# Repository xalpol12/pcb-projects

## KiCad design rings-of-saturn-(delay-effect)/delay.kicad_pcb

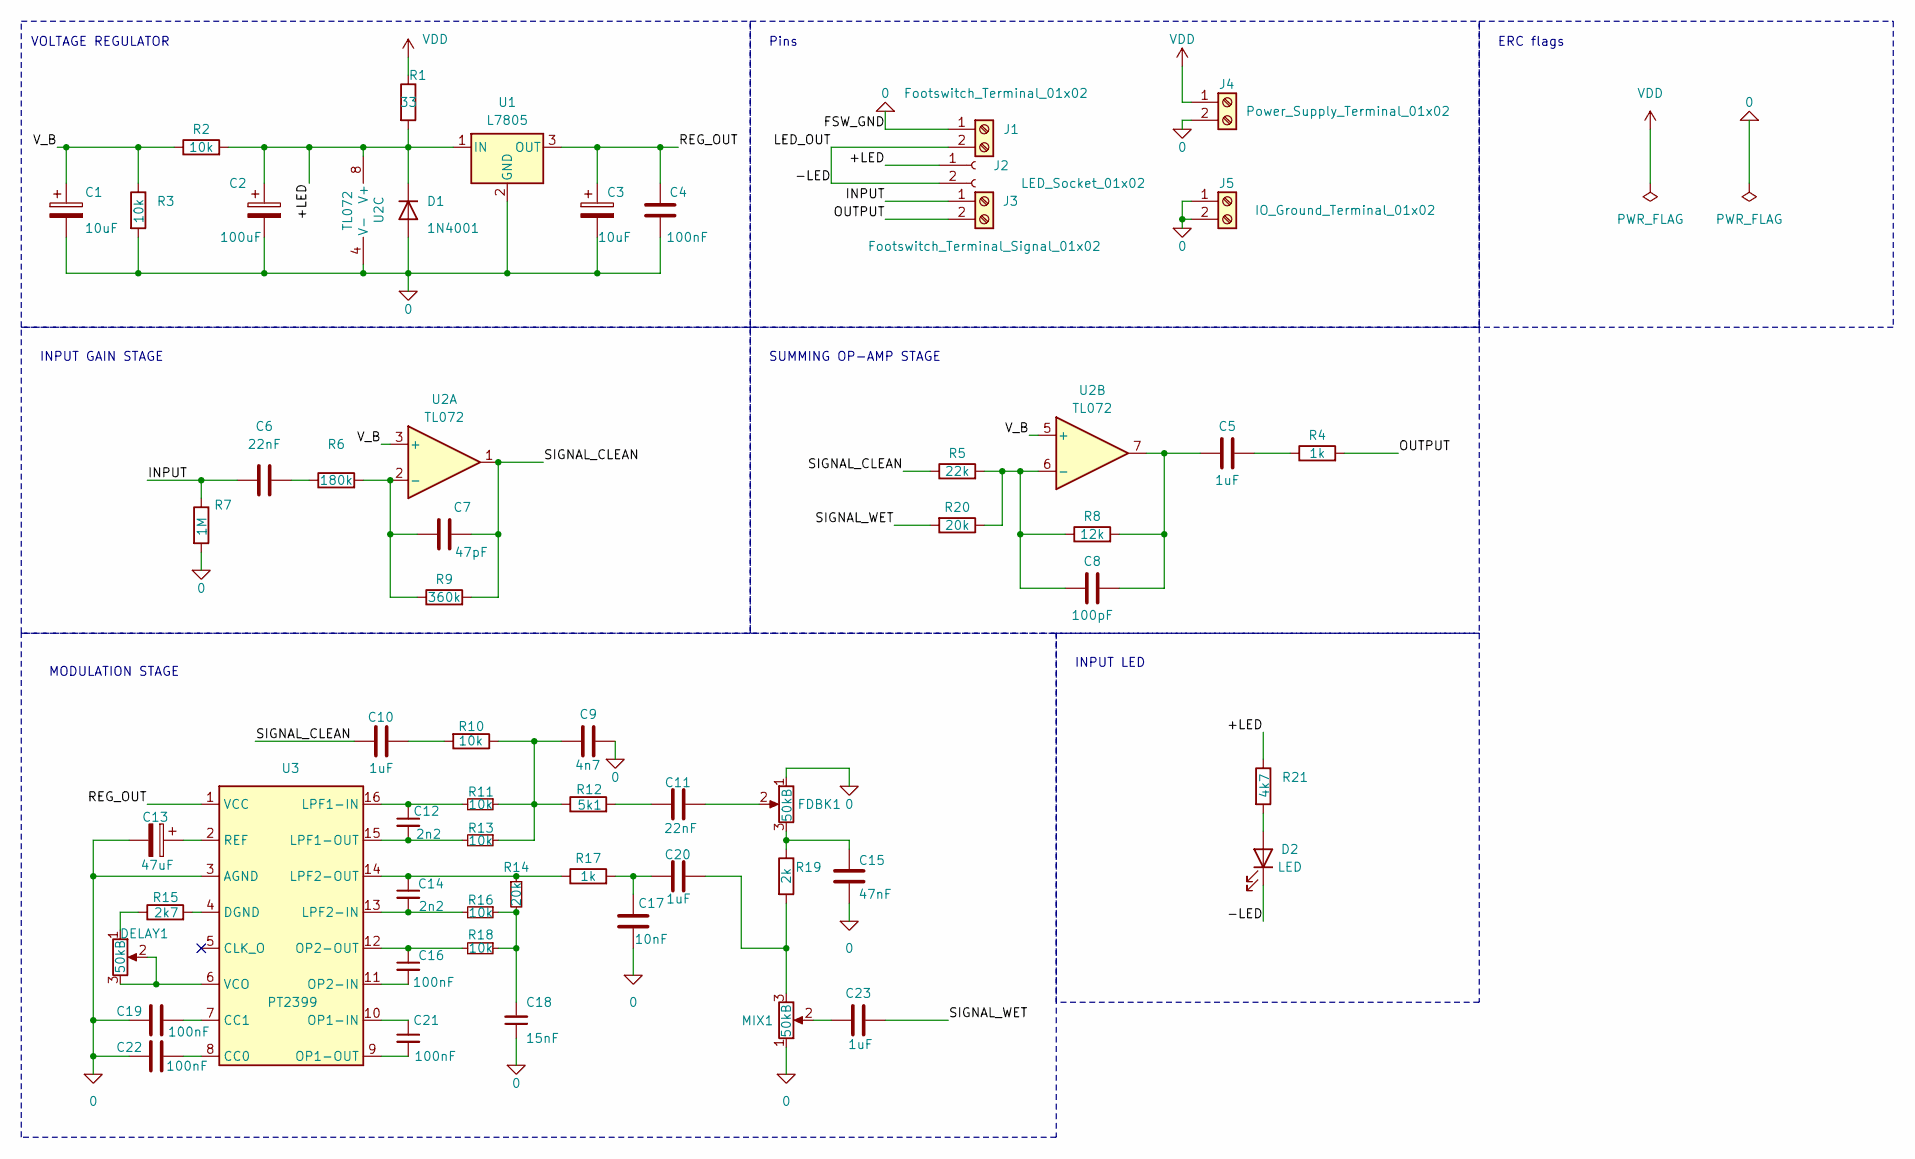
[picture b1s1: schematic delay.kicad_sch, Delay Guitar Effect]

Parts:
C1, C3: 10uF; EEE1AA220WR
C2: 100uF; EEE1AA101SP
C4, C16, C19, C21, C22: 100nF; C_0805_2012Metric_Pad1.18x1.45mm_HandSolder
C5, C10, C20, C23: 1uF; C_0805_2012Metric_Pad1.18x1.45mm_HandSolder
C6, C11: 22nF; C_0805_2012Metric_Pad1.18x1.45mm_HandSolder
C7: 47pF; C_0805_2012Metric_Pad1.18x1.45mm_HandSolder
C8: 100pF; C_0805_2012Metric_Pad1.18x1.45mm_HandSolder
C9: 4n7; C_0805_2012Metric_Pad1.18x1.45mm_HandSolder
C12, C14: 2n2; C_0805_2012Metric_Pad1.18x1.45mm_HandSolder
C13: 47uF; EEE1AA101SP
C15: 47nF; C_0805_2012Metric_Pad1.18x1.45mm_HandSolder
C17: 10nF; C_0805_2012Metric_Pad1.18x1.45mm_HandSolder
C18: 15nF; C_0805_2012Metric_Pad1.18x1.45mm_HandSolder
D1: 1N4001; DIOM5226X240N
D2: LED; TB00150002BE
DELAY1: 50kB; Potentiometer_Alps_RK163_Single_Horizontal
FDBK1: 50kB; Potentiometer_Alps_RK163_Single_Horizontal
J1: Footswitch_Terminal_01x02; TB00150002BE
J2: LED_Socket_01x02; TB00150002BE
J3: Footswitch_Terminal_Signal_01x02; TB00150002BE
J4: Power_Supply_Terminal_01x02; TB00150002BE
J5: IO_Ground_Terminal_01x02; TB00150002BE
MIX1: 50kB; Potentiometer_Alps_RK163_Single_Horizontal
R1: 33; R_0805_2012Metric_Pad1.20x1.40mm_HandSolder
R2, R3, R10, R11, R13, R16, R18: 10k; R_0805_2012Metric_Pad1.20x1.40mm_HandSolder
R4, R17: 1k; R_0805_2012Metric_Pad1.20x1.40mm_HandSolder
R5: 22k; R_0805_2012Metric_Pad1.20x1.40mm_HandSolder
R6: 180k; R_0805_2012Metric_Pad1.20x1.40mm_HandSolder
R7: 1M; R_0805_2012Metric_Pad1.20x1.40mm_HandSolder
R8: 12k; R_0805_2012Metric_Pad1.20x1.40mm_HandSolder
R9: 360k; R_0805_2012Metric_Pad1.20x1.40mm_HandSolder
R12: 5k1; R_0805_2012Metric_Pad1.20x1.40mm_HandSolder
R14, R20: 20k; R_0805_2012Metric_Pad1.20x1.40mm_HandSolder
R15: 2k7; R_0805_2012Metric_Pad1.20x1.40mm_HandSolder
R19: 2k; R_0805_2012Metric_Pad1.20x1.40mm_HandSolder
R21: 4k7; R_0805_2012Metric_Pad1.20x1.40mm_HandSolder
U1: L7805; L7805CD2T
U2: TL072; SOT65P280X110-8N
U3: PT2399; SOIC-16_3.9x9.9mm_P1.27mm

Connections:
0: C1.2, C2.2, C3.2, C4.2, C9.2, C13.2, C15.2, C17.1, C18.1, C19.2, C22.2, D1.2 (A), FDBK1.1, J1.1, J4.2, J5.1, J5.2, MIX1.1, R3.2, R7.2, U1.2 (GND), U2.4 (V-), U3.3 (AGND)
/+LED: C2.1, D1.1 (K), J2.1, R1.2, R2.2, R21.1, U1.1 (IN), U2.8 (V+)
/-LED: D2.1 (K), J1.2, J2.2
/INPUT: C6.1, J3.1, R7.1
/OUTPUT: J3.2, R4.2
/REG_OUT: C3.1, C4.1, U1.3 (OUT), U3.1 (VCC)
/SIGNAL_CLEAN: C7.2, C10.2, R5.1, R9.2, U2.1
/SIGNAL_WET: C23.2, R20.2
/V_B: C1.1, R2.1, R3.1, U2.3 (+), U2.5 (+)
unnamed: C5.1, C8.2, R8.2, U2.7
unnamed: C5.2, R4.1
unnamed: C6.2, R6.1
unnamed: C9.1, R10.1, R11.1, R12.1, R13.1
unnamed: C10.1, R10.2
unnamed: C11.1, R12.2
unnamed: C11.2, FDBK1.2
unnamed: C15.1, FDBK1.3, R19.1
unnamed: C17.2, C20.1, R17.2
unnamed: C18.2, R14.2, R16.1, R18.1
unnamed: C20.2, MIX1.3, R19.2
unnamed: C23.1, MIX1.2
unnamed: D2.2 (A), R21.2
unnamed: DELAY1.1, R15.1
unnamed: C7.1, R6.2, R9.1, U2.2 (-)
unnamed: C8.1, R5.2, R8.1, R20.1, U2.6 (-)
unnamed: C22.1, U3.8 (CC0)
unnamed: C19.1, U3.7 (CC1)
unnamed: R15.2, U3.4 (DGND)
unnamed: C12.1, R11.2, U3.16 (LPF1-IN)
unnamed: C12.2, R13.2, U3.15 (LPF1-OUT)
unnamed: C14.2, R16.2, U3.13 (LPF2-IN)
unnamed: C14.1, R14.1, R17.1, U3.14 (LPF2-OUT)
unnamed: C21.1, U3.10 (OP1-IN)
unnamed: C21.2, U3.9 (OP1-OUT)
unnamed: C16.2, U3.11 (OP2-IN)
unnamed: C16.1, R18.2, U3.12 (OP2-OUT)
unnamed: C13.1, U3.2 (REF)
unnamed: DELAY1.2, DELAY1.3, U3.6 (VCO)
VDD: J4.1, R1.1

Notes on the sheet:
ERC flags
MODULATION STAGE
SUMMING OP-AMP STAGE
INPUT LED
INPUT GAIN STAGE
Pins
VOLTAGE REGULATOR

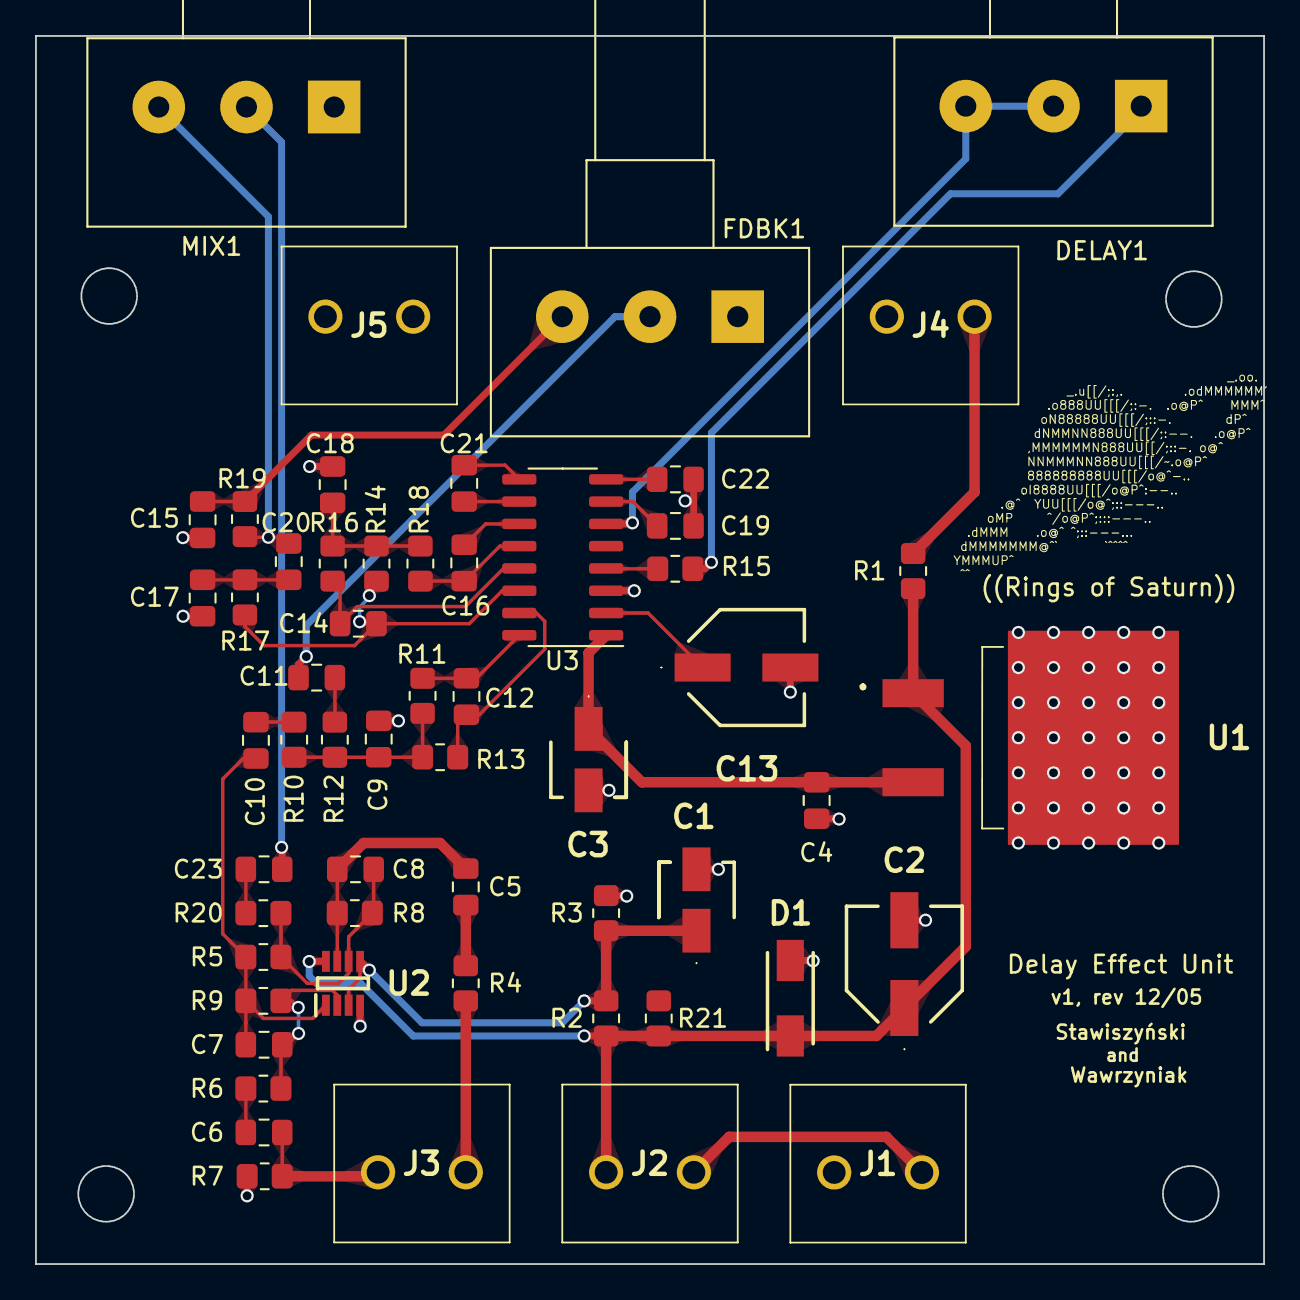
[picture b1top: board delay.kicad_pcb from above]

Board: 2 copper layers, 70.0 x 70.0 mm, 56 parts (0 on the bottom side), 38 nets.

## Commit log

2023-11-06 init
2023-11-06 add ref materials
2023-11-06 add footprint for each element
2023-11-07 add list of components and respective links, add real footprints
2023-11-10 add screw connectors
2023-11-11 update design rules for pcb creator to match requirements
2023-11-13 add remaining footprints, start pcb design process
2023-11-15 create preliminary pcb spacing design
2023-11-15 add some connections (first draw)
2023-11-19 update pcb design schema
2023-11-19 create preliminary design schema with internal connections
2023-11-20 create connections for all signals except 0
2023-11-20 connect mass and reorganise labels
2023-11-21 modify ground layer positioning
2023-11-22 update pcb design
2023-11-24 add ground vias inside stabilisator GND field, add board revision info
2023-12-04 improve ground plane design, add thicker routes to audio paths
2023-12-04 refactor pcb design, reduce board size to 70x70
2023-12-05 add pcb mounting holes
2023-12-05 small track thickness and area keepout adjustments
2023-12-06 fine tune ground vias distance from components
2023-12-07 create subfolder for ring of saturn project
2023-12-11 add .gitignore with backup files
2023-12-11 reset file tracking for rings-of-saturn directory
2023-12-17 init fuzz-effect project (based on big muff guitar pedal)
2023-12-18 fuzz effect first schematic draft, add reference files
